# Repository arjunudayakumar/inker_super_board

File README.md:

# inker_super_board
Inker Super Board is a development tool for school students. It can be used in various projects
from a simple line follower to image processing

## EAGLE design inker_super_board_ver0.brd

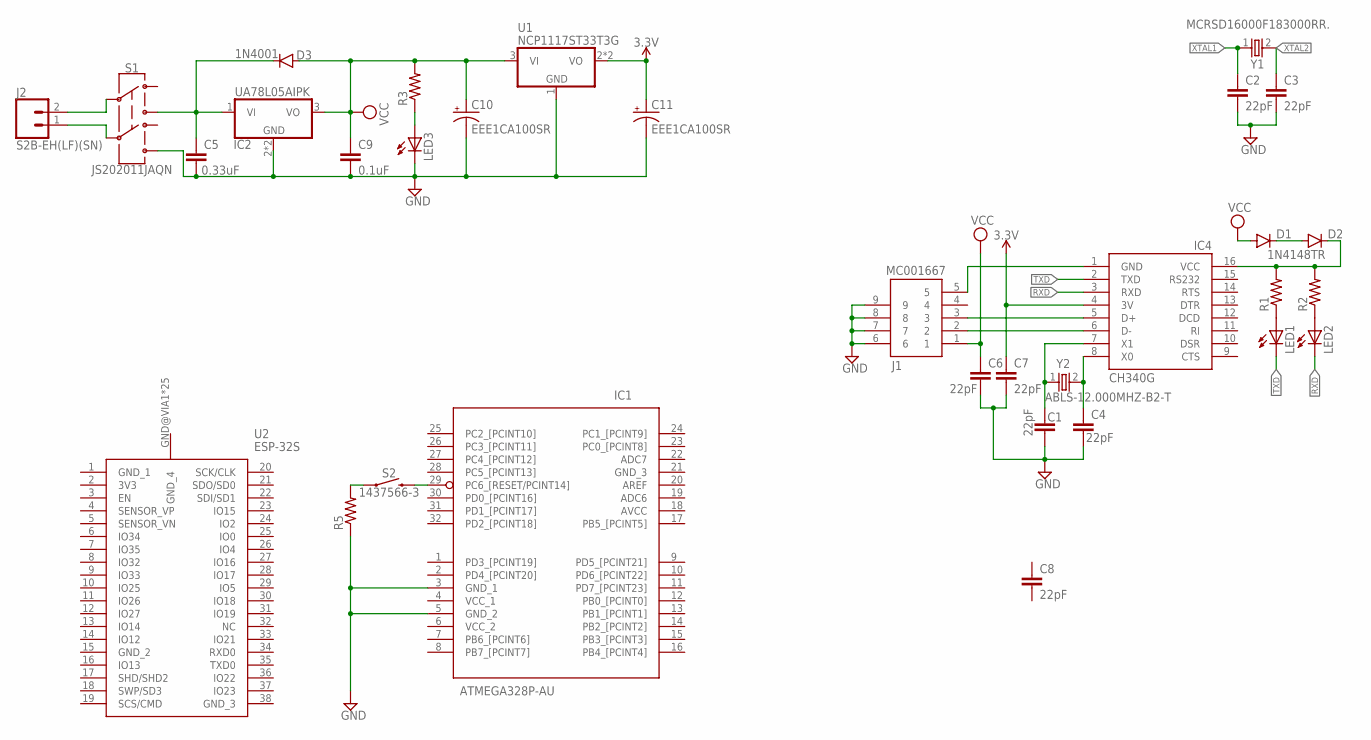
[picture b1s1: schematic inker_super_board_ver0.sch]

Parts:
C1, C2, C3, C4, C6, C7, C8: 22pF; 0603
C5: 0.33uF; 0805
C9: 0.1uF; 0805
C10, C11: EEE1CA100SR
D1, D2: 1N4148TR; DIOAD990W55L340D162
D3: 1N4001; DIOAD1405W86L465D235
IC1: ATMEGA328P-AU; QFP80P900X900X120-32N
IC2: UA78L05AIPK; PK(R-PSSO-F3)
IC4: CH340G; SO16
J1: MC001667
J2: S2B-EH(LF)(SN); SHDR2W64P0X250_1X2_750X820X420
LED1, LED2, LED3: LEDCHIP-LED0805; CHIP-LED0805
R1, R2, R3, R5: R-US_R0805; R0805
S1: JS202011JAQN
S2: 1437566-3; 14375663
U1: NCP1117ST33T3G; SOT230P700X180-4N
U2: ESP-32S
Y1: MCRSD16000F183000RR.; MCRSD16000F183000RR
Y2: ABLS-12.000MHZ-B2-T; ABLS-12.000MHZ-B2

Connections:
3.3V: C7.1, C11.1 (+), IC4.4 (3V), U1.2 (VO), U1.4 (VO)
AVCC: IC1.18 (AVCC)
GND: C1.2, C2.2, C3.2, C4.2, C5.2, C6.2, C7.2, C9.2, C10.2 (-), C11.2 (-), IC1.3 (GND_1), IC1.5 (GND_2), IC2.2 (GND), IC2.4 (GND), J1.6, J1.7, J1.8, J1.9, LED3.C, R5.1, S1.6, U1.1 (GND)
GND_3: IC1.21 (GND_3)
unnamed: LED1.A, R1.1
unnamed: LED2.A, R2.1
unnamed: LED3.A, R3.1
unnamed: IC1.29 (PC6_[RESET/PCINT14]), S2.2
unnamed: R5.2, S2.1
unnamed: C1.1, IC4.7 (X1), Y2.1
unnamed: C4.1, IC4.8 (X0), Y2.2
unnamed: D2.1 (C), IC4.16 (VCC), R1.2, R2.2
unnamed: D1.1 (C), D2.2 (A)
unnamed: IC4.6 (D-), J1.2
unnamed: IC4.5 (D+), J1.3
unnamed: J2.2, S1.2
unnamed: J2.1, S1.5
unnamed: IC4.1 (GND), J1.5
RXD: IC4.3 (RXD), LED2.C
TXD: IC4.2 (TXD), LED1.C
VCC: C6.1, C9.1, C10.1 (+), D1.2 (A), D3.2 (A), IC2.3 (VO), J1.1, R3.2, U1.3 (VI)
VCC_1: IC1.4 (VCC_1)
VCC_2: IC1.6 (VCC_2)
VIN: C5.1, D3.1 (C), IC2.1 (VI), S1.3
XTAL1: C2.1, Y1.1
XTAL2: C3.1, Y1.2

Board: 2 copper layers, 32 parts (1 on the bottom side), 22 nets, no tracks yet.

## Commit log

2020-02-03 Schematic Capture
2020-02-03 Added git ignore
2020-02-03 Added gitignore

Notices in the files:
parts and their libraries:
SparkFun-Capacitors: Licensing: Creative Commons ShareAlike 4.0 International - https://creativecommons.org/licenses/by-sa/4.0
COPYRIGHT: Copyright (C) 2016 Accelerated Designs. All rights reserved
